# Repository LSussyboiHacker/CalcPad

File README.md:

# CalcPad
My custom calculator macropad, will be used to calculate.

BOM

- 16x Blank DSA Keycaps
- 4x M3x16 Bolt
- 4x M3 Heatset
- 1x XIAO RP2040
- 16x Cherry MX Switches
- 1x 3D printed case (top and bottom)
- 1x 0.91 inch OLED display
- 16x Through-hole 1N4148 Diodes

Schematic

PCB

CAD

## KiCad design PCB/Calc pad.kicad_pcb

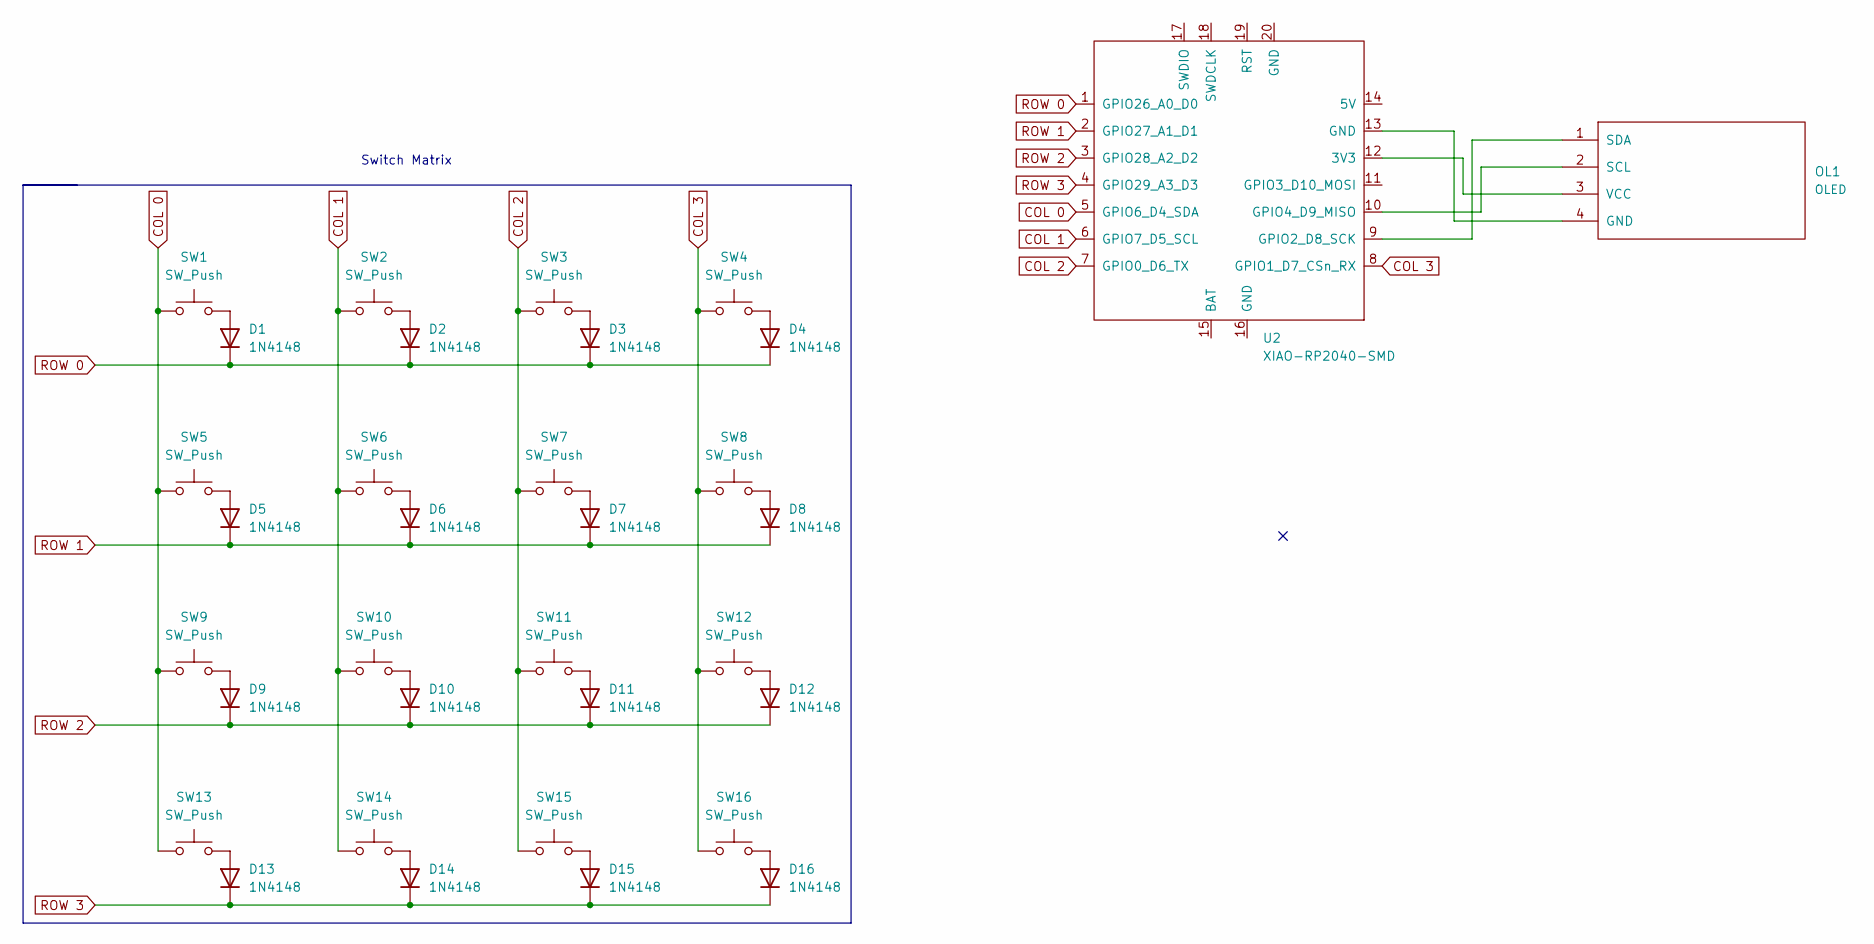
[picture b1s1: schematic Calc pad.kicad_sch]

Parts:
D1, D2, D3, D4, D5, D6, D7, D8, D9, D10, D11, D12, D13, D14, D15, D16: 1N4148; D_DO-35_SOD27_P7.62mm_Horizontal
OL1: OLED; PinHeader_1x04_P2.54mm_Vertical
SW1, SW2, SW3, SW4, SW5, SW6, SW7, SW8, SW9, SW10, SW11, SW12, SW13, SW14, SW15, SW16: SW_Push; SW_Cherry_MX_1.00u_PCB
U2: XIAO-RP2040-SMD

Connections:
COL 0: SW1.1, SW5.1, SW9.1, SW13.1, U2.5 (GPIO6_D4_SDA)
COL 1: SW2.1, SW6.1, SW10.1, SW14.1, U2.6 (GPIO7_D5_SCL)
COL 2: SW3.1, SW7.1, SW11.1, SW15.1, U2.7 (GPIO0_D6_TX)
COL 3: SW4.1, SW8.1, SW12.1, SW16.1, U2.8 (GPIO1_D7_CSn_RX)
unnamed: D1.2 (A), SW1.2
unnamed: D2.2 (A), SW2.2
unnamed: D3.2 (A), SW3.2
unnamed: D4.2 (A), SW4.2
unnamed: D5.2 (A), SW5.2
unnamed: D6.2 (A), SW6.2
unnamed: D7.2 (A), SW7.2
unnamed: D8.2 (A), SW8.2
unnamed: D9.2 (A), SW9.2
unnamed: D10.2 (A), SW10.2
unnamed: D11.2 (A), SW11.2
unnamed: D12.2 (A), SW12.2
unnamed: D13.2 (A), SW13.2
unnamed: D14.2 (A), SW14.2
unnamed: D15.2 (A), SW15.2
unnamed: D16.2 (A), SW16.2
unnamed: OL1.4 (GND), U2.13 (GND)
unnamed: OL1.2 (SCL), U2.10 (GPIO4_D9_MISO)
unnamed: OL1.1 (SDA), U2.9 (GPIO2_D8_SCK)
unnamed: OL1.3 (VCC), U2.12 (3V3)
ROW 0: D1.1 (K), D2.1 (K), D3.1 (K), D4.1 (K), U2.1 (GPIO26_A0_D0)
ROW 1: D5.1 (K), D6.1 (K), D7.1 (K), D8.1 (K), U2.2 (GPIO27_A1_D1)
ROW 2: D9.1 (K), D10.1 (K), D11.1 (K), D12.1 (K), U2.3 (GPIO28_A2_D2)
ROW 3: D13.1 (K), D14.1 (K), D15.1 (K), D16.1 (K), U2.4 (GPIO29_A3_D3)

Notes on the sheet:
Switch Matrix

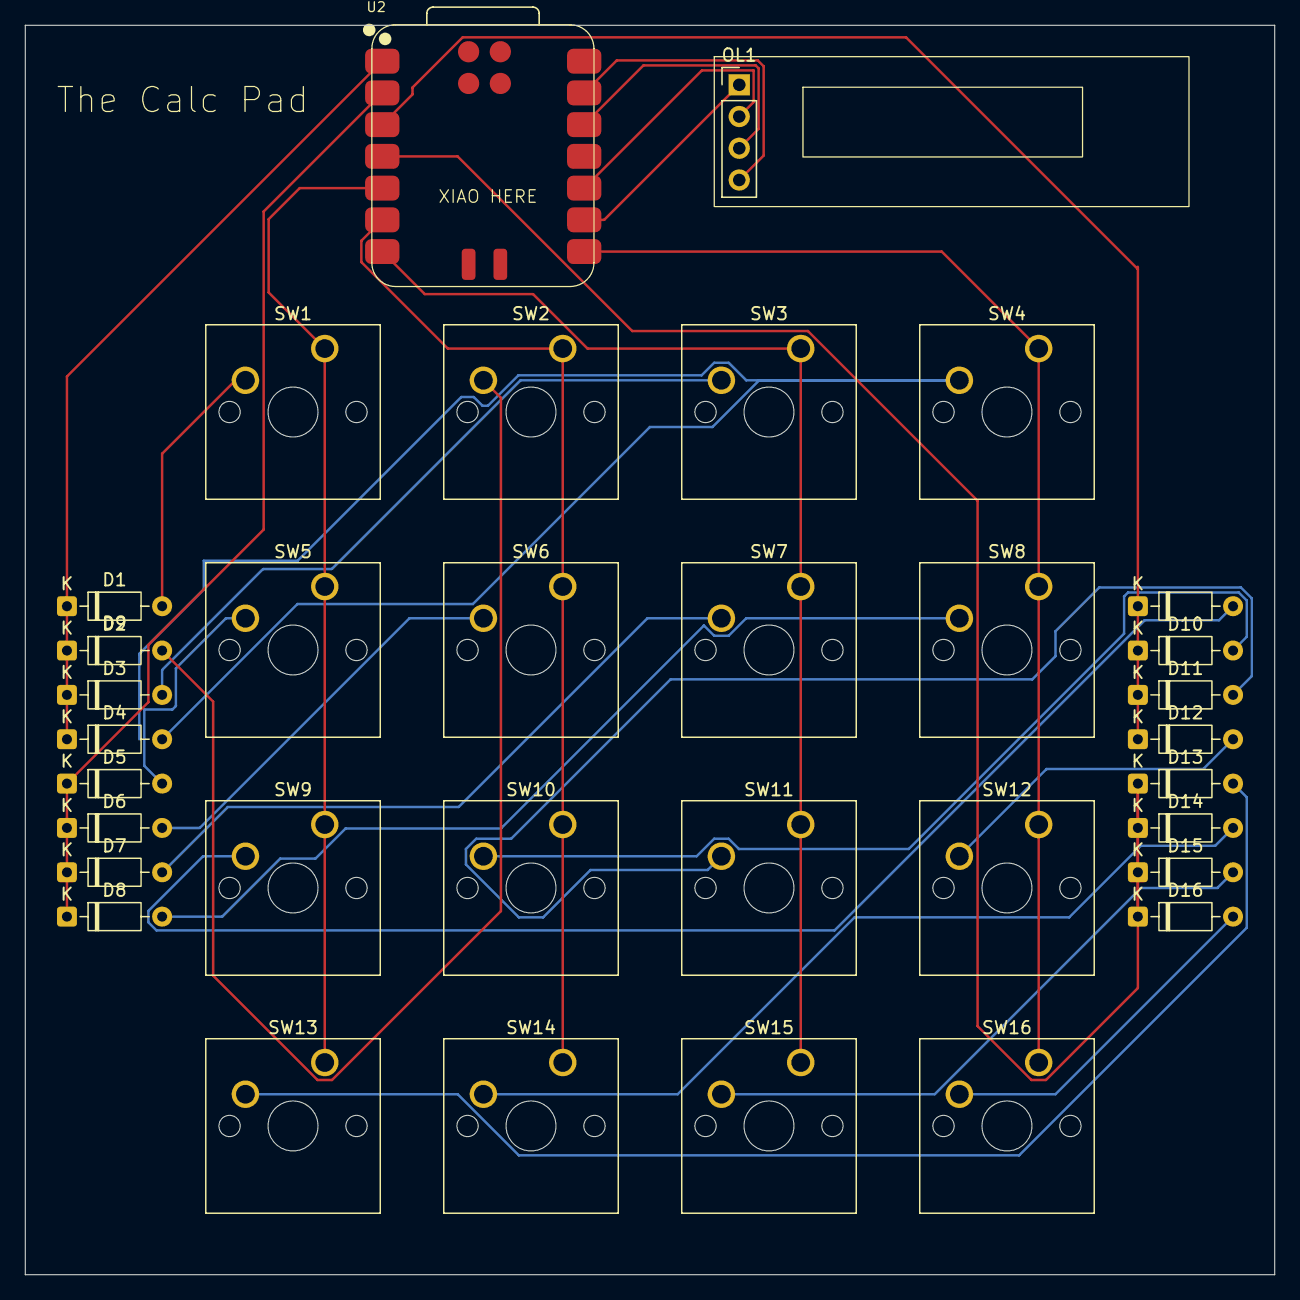
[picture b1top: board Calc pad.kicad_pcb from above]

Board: 2 copper layers, 100.0 x 100.0 mm, 34 parts (0 on the bottom side), 28 nets.

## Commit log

2026-01-07 file upload
2026-01-07 Expand README with BOM, schematic, PCB, and CAD
    Added Bill of Materials (BOM), schematic, PCB, and CAD images.
